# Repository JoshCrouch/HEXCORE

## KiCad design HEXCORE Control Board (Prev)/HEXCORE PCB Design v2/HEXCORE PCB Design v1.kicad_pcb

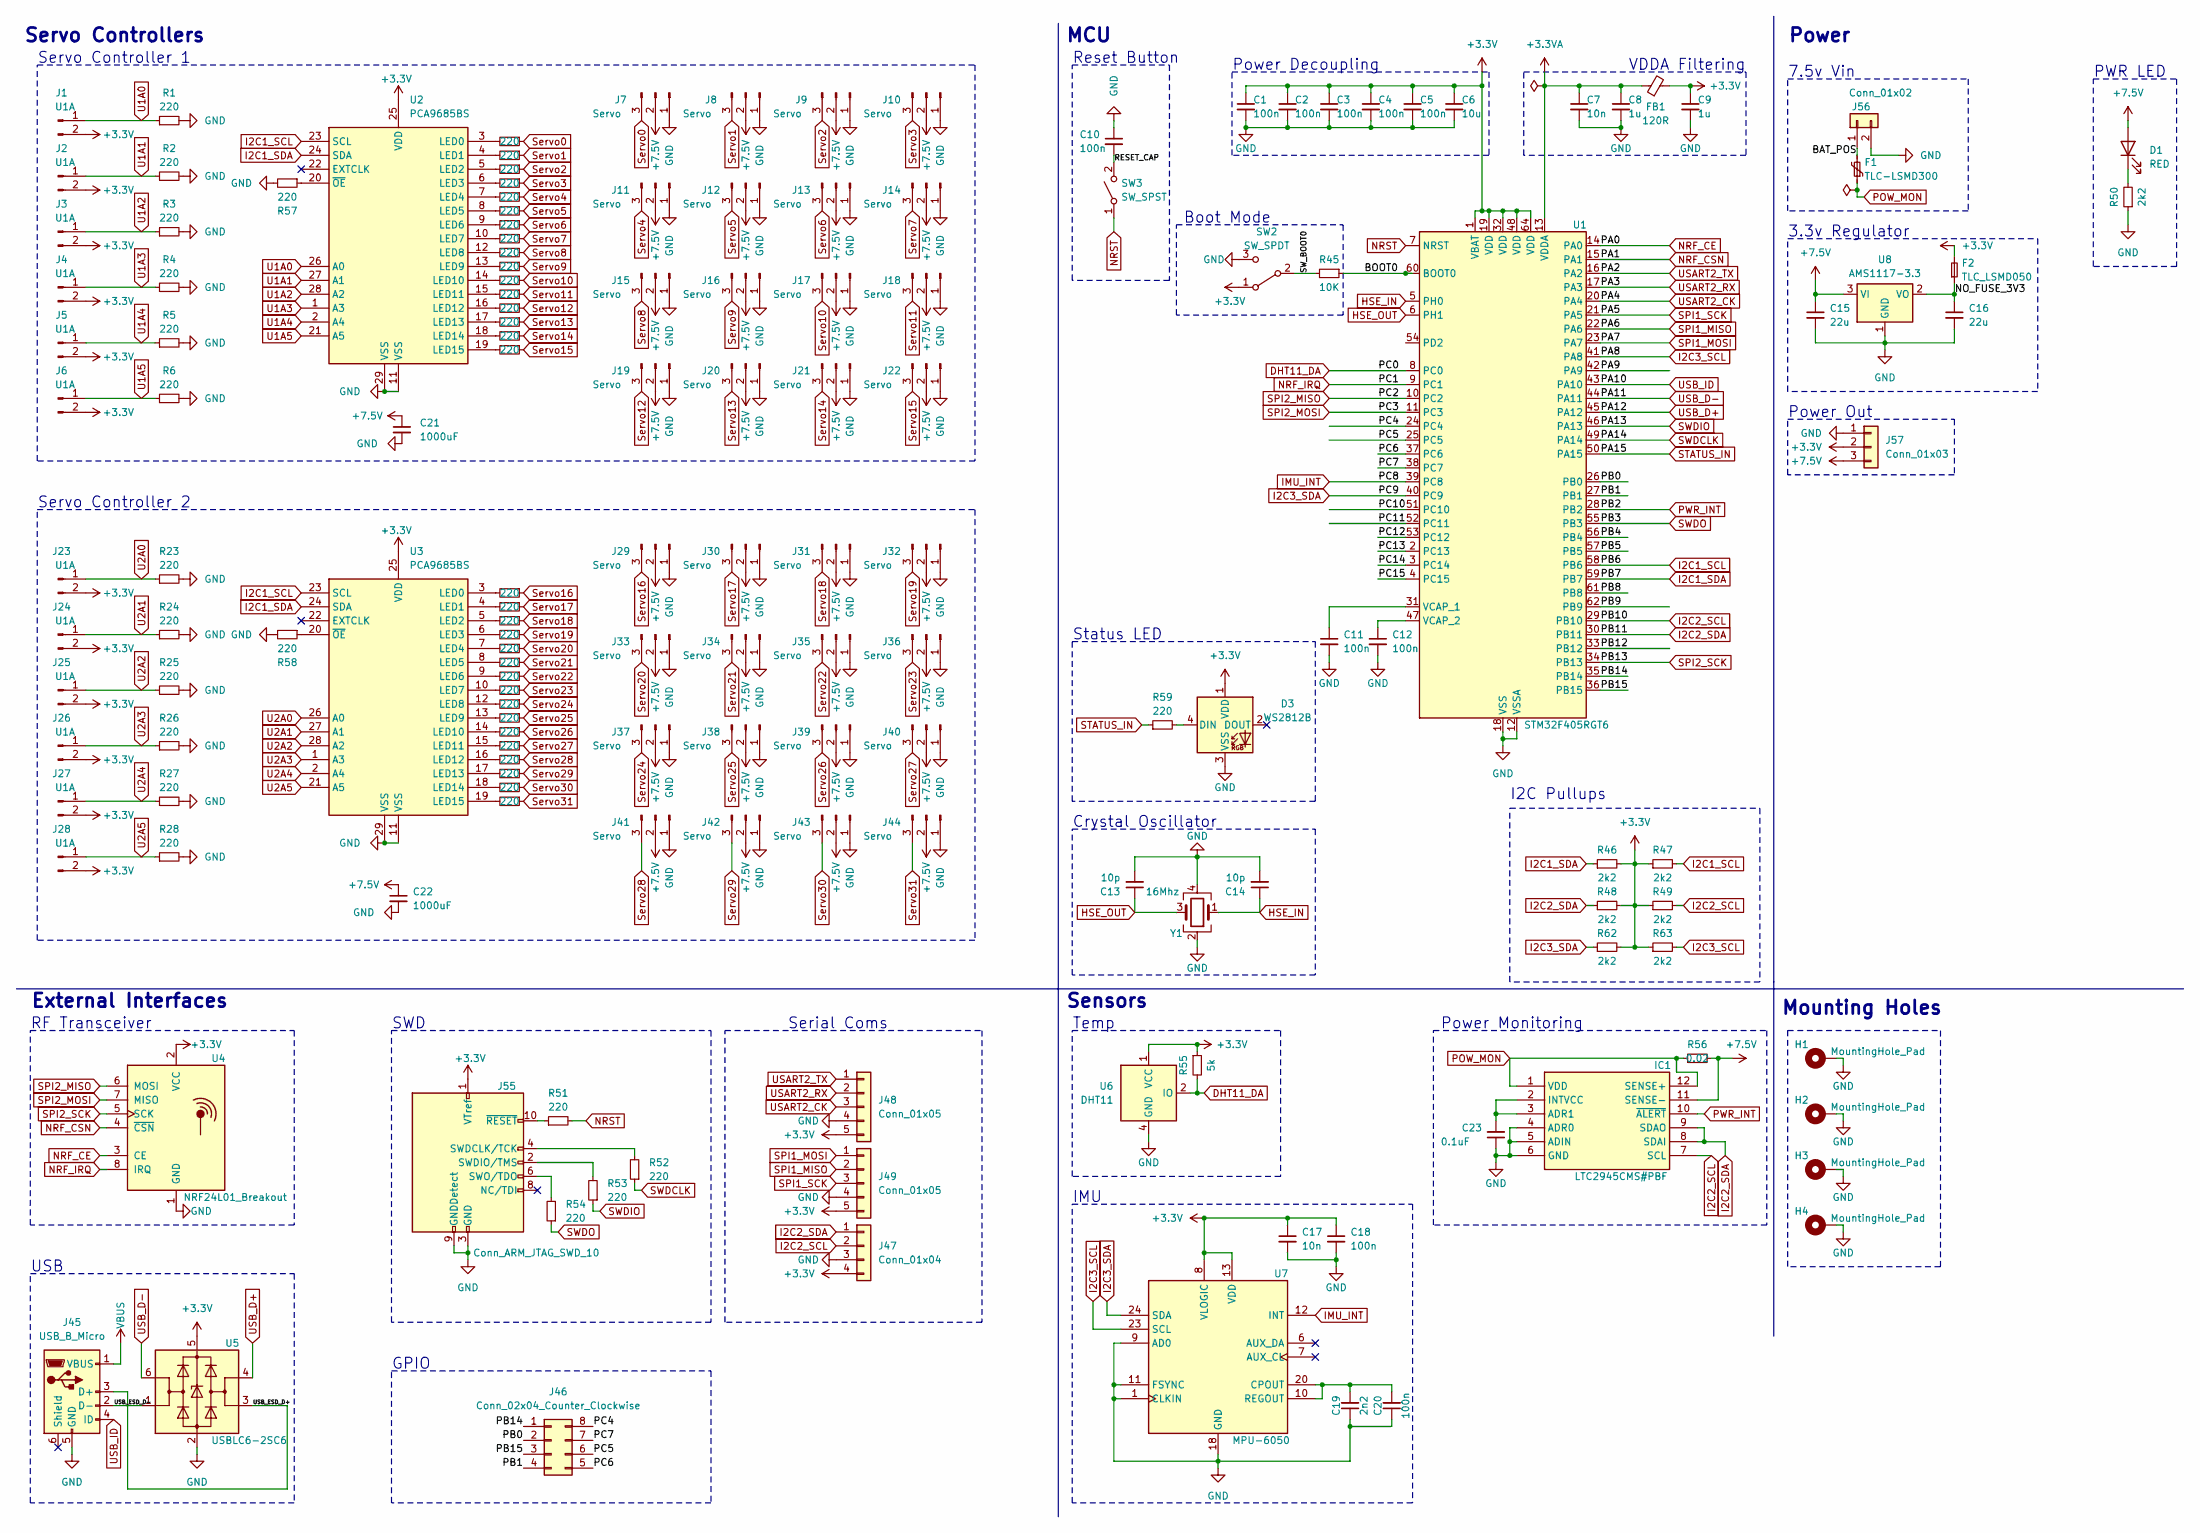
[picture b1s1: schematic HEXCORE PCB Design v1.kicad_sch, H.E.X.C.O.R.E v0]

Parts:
C1, C2, C3, C4, C5, C11, C12: 100n; C_0402_1005Metric
C6: 10u; C_0603_1608Metric
C7: 10n; C_0402_1005Metric
C8, C9: 1u; C_0402_1005Metric
C10, C18, C20: 100n; C_0201_0603Metric
C13, C14: 10p; C_0201_0603Metric
C15, C16: 22u; C_0603_1608Metric
C17: 10n; C_0201_0603Metric
C19: 2n2; C_0201_0603Metric
C21, C22: 1000uF; C_Elec_10x10.2
C23: 0.1uF; C_0201_0603Metric
D1: RED; LED_0603_1608Metric; LCSC Part C2286
D3: WS2812B; LED_WS2812B_PLCC4_5.0x5.0mm_P3.2mm; LCSC Part C2843785
F1: TLC-LSMD300; Fuse_2920_7451Metric; LCSC Part C262042
F2: TLC_LSMD050; Fuse_2920_7451Metric; LCSC Part C262037
FB1: 120R; L_0603_1608Metric
H1, H2, H3, H4: MountingHole_Pad; MountingHole_2.2mm_M2_DIN965_Pad
IC1: LTC2945CMS#PBF; SOP65P490X110-12N; Manufacturer_Part_Number LTC2945CMS#PBF; Mouser Part Number 584-LTC2945CMS#PBF
J1, J2, J3, J4, J5, J6, J23, J24, J25, J26, J27, J28: U1A; PinHeader_1x02_P2.54mm_Vertical
J7, J8, J9, J10, J11, J12, J13, J14, J15, J16, J17, J18, J19, J20, J21, J22, J29, J30, J31, J32, J33, J34, J35, J36, J37, J38, J39, J40, J41, J42, J43, J44: Servo; PinHeader_1x03_P2.54mm_Vertical
J45: USB_B_Micro; MICROXNJ; LCSC Part C404969
J46: Conn_02x04_Counter_Clockwise; PinSocket_2x04_P2.54mm_Vertical
J47: Conn_01x04; JST_XH_B4B-XH-A_1x04_P2.50mm_Vertical
J48, J49: Conn_01x05; JST_XH_B5B-XH-A_1x05_P2.50mm_Vertical
J55: Conn_ARM_JTAG_SWD_10; PinHeader_2x05_P1.27mm_Vertical
J56: Conn_01x02; AMASS_XT60-M_1x02_P7.20mm_Vertical; LCSC Part C98733
J57: Conn_01x03; JST_XH_B3B-XH-A_1x03_P2.50mm_Vertical
R1, R2, R3, R4, R5, R6, R7, R8, R9, R10, R11, R12, R13, R14, R15, R16, R17, R18, R19, R20, R21, R22, R23, R24, R25, R26, R27, R28, R29, R30, R31, R32, R33, R34, R35, R36, R37, R38, R39, R40, R41, R42, R43, R44, R51, R52, R53, R54, R57, R58, R59: 220; R_0201_0603Metric
R45: 10K; R_0201_0603Metric
R46, R47, R48, R49, R50, R62, R63: 2k2; R_0402_1005Metric
R55: 5k; R_0402_1005Metric
R56: 0.02; R_2512_6332Metric
SW2: SW_SPDT; SW_Slide_1P2T_CK_OS102011MS2Q; LCSC Part C2800116
SW3: SW_SPST; SW_SPST_B3S-1000; LCSC Part C180420
U1: STM32F405RGT6; LQFP-64_10x10mm_P0.5mm; LCSC Part C15742
U2, U3: PCA9685BS; QFN-28-1EP_6x6mm_P0.65mm_EP4.25x4.25mm; LCSC Part C5191634
U4: NRF24L01_Breakout; nRF24L01_Breakout
U5: USBLC6-2SC6; SOT-23-6; LCSC Part C2827654
U6: DHT11; Aosong_DHT11_5.5x12.0_P2.54mm; LCSC Part C117051
U7: MPU-6050; InvenSense_QFN-24_4x4mm_P0.5mm; LCSC Part C24112
U8: AMS1117-3.3; SOT-223-3_TabPin2; LCSC Part C347222
Y1: 16Mhz; Crystal_SMD_2520-4Pin_2.5x2.0mm; LCSC Part C255947

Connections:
+3.3V: C1.1, C2.1, C3.1, C4.1, C5.1, C6.1, C9.1, C17.1, C18.1, D3.1 (VDD), F2.2, FB1.2, J1.2, J2.2, J3.2, J4.2, J5.2, J6.2, J23.2, J24.2, J25.2, J26.2, J27.2, J28.2, J47.4, J48.5, J49.5, J55.1 (VTref), J57.2, R46.2, R47.1, R48.2, R49.1, R55.1, R62.2, R63.1, SW2.1 (A), U1.1 (VBAT), U1.19 (VDD), U1.32 (VDD), U1.48 (VDD), U1.64 (VDD), U2.25 (VDD), U3.25 (VDD), U4.2 (VCC), U5.5 (VBUS), U6.1 (VCC), U7.8 (VLOGIC), U7.13 (VDD)
+3.3VA: C7.1, C8.1, FB1.1, U1.13 (VDDA)
+7.5V: C15.1, C21.1, C22.1, D1.2 (A), IC1.11 (SENSE-), J7.2, J8.2, J9.2, J10.2, J11.2, J12.2, J13.2, J14.2, J15.2, J16.2, J17.2, J18.2, J19.2, J20.2, J21.2, J22.2, J29.2, J30.2, J31.2, J32.2, J33.2, J34.2, J35.2, J36.2, J37.2, J38.2, J39.2, J40.2, J41.2, J42.2, J43.2, J44.2, J57.3, R56.2, U8.3 (VI)
/BAT_POS: F1.2, J56.1
/BOOT0: R45.1, U1.60 (BOOT0)
/NO_FUSE_3V3: C16.1, F2.1, U8.2 (VO)
/PA9: U1.42 (PA9)
/PB0: J46.2, U1.26 (PB0)
/PB1: J46.4, U1.27 (PB1)
/PB4: U1.56 (PB4)
/PB5: U1.57 (PB5)
/PB8: U1.61 (PB8)
/PB9: U1.62 (PB9)
/PB12: U1.33 (PB12)
/PB14: J46.1, U1.35 (PB14)
/PB15: J46.3, U1.36 (PB15)
/PC4: J46.8, U1.24 (PC4)
/PC5: J46.6, U1.25 (PC5)
/PC6: J46.5, U1.37 (PC6)
/PC7: J46.7, U1.38 (PC7)
/PC10: U1.51 (PC10)
/PC11: U1.52 (PC11)
/PC12: U1.53 (PC12)
/PC13: U1.2 (PC13)
/PC14: U1.3 (PC14)
/PC15: U1.4 (PC15)
/RESET_CAP: C10.2, SW3.2 (B)
/SW_BOOT0: R45.2, SW2.2 (B)
/USB_ESD_D+: J45.3 (D+), U5.3 (I/O2)
/USB_ESD_D-: J45.2 (D-), U5.1 (I/O1)
DHT11_DA: R55.2, U1.8 (PC0), U6.2 (IO)
GND: C1.2, C2.2, C3.2, C4.2, C5.2, C6.2, C7.2, C8.2, C9.2, C10.1, C11.2, C12.2, C13.2, C14.2, C15.2, C16.2, C17.2, C18.2, C19.1, C20.1, C21.2, C22.2, C23.1, D3.3 (VSS), H1.1, H2.1, H3.1, H4.1, IC1.4 (ADR0), IC1.5 (ADIN), IC1.6 (GND), J7.1, J8.1, J9.1, J10.1, J11.1, J12.1, J13.1, J14.1, J15.1, J16.1, J17.1, J18.1, J19.1, J20.1, J21.1, J22.1, J29.1, J30.1, J31.1, J32.1, J33.1, J34.1, J35.1, J36.1, J37.1, J38.1, J39.1, J40.1, J41.1, J42.1, J43.1, J44.1, J45.5 (GND), J47.3, J48.4, J49.4, J55.3 (GND), J55.5 (GND), J55.9 (GNDDetect), J56.2, J57.1, R1.2, R2.2, R3.2, R4.2, R5.2, R6.2, R23.2, R24.2, R25.2, R26.2, R27.2, R28.2, R50.1, R57.2, R58.2, SW2.3 (C), U1.12 (VSSA), U1.18 (VSS), U1.63 (VSS), U2.11 (VSS), U2.29 (VSS), U3.11 (VSS), U3.29 (VSS), U4.1 (GND), U5.2 (GND), U6.4 (GND), U7.1 (CLKIN), U7.9 (AD0), U7.11 (FSYNC), U7.18 (GND), U8.1 (GND), Y1.2, Y1.4
HSE_IN: C14.1, U1.5 (PH0), Y1.1
HSE_OUT: C13.1, U1.6 (PH1), Y1.3
I2C1_SCL: R47.2, U1.58 (PB6), U2.23 (SCL), U3.23 (SCL)
I2C1_SDA: R46.1, U1.59 (PB7), U2.24 (SDA), U3.24 (SDA)
I2C2_SCL: IC1.7 (SCL), J47.2, R49.2, U1.29 (PB10)
I2C2_SDA: IC1.8 (SDAI), IC1.9 (SDAO), J47.1, R48.1, U1.30 (PB11)
I2C3_SCL: R63.2, U1.41 (PA8), U7.23 (SCL)
I2C3_SDA: R62.1, U1.40 (PC9), U7.24 (SDA)
IMU_INT: U1.39 (PC8), U7.12 (INT)
NRF_CE: U1.14 (PA0), U4.3 (CE)
NRF_CSN: U1.15 (PA1), U4.4 (~CSN)
NRF_IRQ: U1.9 (PC1), U4.8 (IRQ)
NRST: R51.2, SW3.1 (A), U1.7 (NRST)
unnamed: D1.1 (K), R50.2
unnamed: D3.4 (DIN), R59.2
unnamed: C23.2, IC1.2 (INTVCC), IC1.3 (ADR1)
unnamed: J55.4 (SWDCLK/TCK), R52.2
unnamed: J55.2 (SWDIO/TMS), R53.2
unnamed: J55.6 (SWO/TDO), R54.2
unnamed: J55.10 (~RESET), R51.1
unnamed: C11.1, U1.31 (VCAP_1)
unnamed: C12.1, U1.47 (VCAP_2)
unnamed: R7.2, U2.3 (LED0)
unnamed: R8.2, U2.4 (LED1)
unnamed: R9.2, U2.5 (LED2)
unnamed: R10.2, U2.6 (LED3)
unnamed: R11.2, U2.7 (LED4)
unnamed: R12.2, U2.8 (LED5)
unnamed: R13.2, U2.9 (LED6)
unnamed: R14.2, U2.10 (LED7)
unnamed: R15.2, U2.12 (LED8)
unnamed: R16.2, U2.13 (LED9)
unnamed: R17.2, U2.14 (LED10)
unnamed: R18.2, U2.15 (LED11)
unnamed: R19.2, U2.16 (LED12)
unnamed: R20.2, U2.17 (LED13)
unnamed: R21.2, U2.18 (LED14)
unnamed: R22.2, U2.19 (LED15)
unnamed: R57.1, U2.20 (~OE)
unnamed: R29.2, U3.3 (LED0)
unnamed: R30.2, U3.4 (LED1)
unnamed: R31.2, U3.5 (LED2)
unnamed: R32.2, U3.6 (LED3)
unnamed: R33.2, U3.7 (LED4)
unnamed: R34.2, U3.8 (LED5)
unnamed: R35.2, U3.9 (LED6)
unnamed: R36.2, U3.10 (LED7)
unnamed: R37.2, U3.12 (LED8)
unnamed: R38.2, U3.13 (LED9)
unnamed: R39.2, U3.14 (LED10)
unnamed: R40.2, U3.15 (LED11)
unnamed: R41.2, U3.16 (LED12)
unnamed: R42.2, U3.17 (LED13)
unnamed: R43.2, U3.18 (LED14)
unnamed: R44.2, U3.19 (LED15)
unnamed: R58.1, U3.20 (~OE)
unnamed: C19.2, C20.2, U7.10 (REGOUT), U7.20 (CPOUT)
POW_MON: F1.1, IC1.1 (VDD), IC1.12 (SENSE+), R56.1
PWR_INT: IC1.10 (~ALERT), U1.28 (PB2)
SPI1_MISO: J49.2, U1.22 (PA6)
SPI1_MOSI: J49.1, U1.23 (PA7)
SPI1_SCK: J49.3, U1.21 (PA5)
SPI2_MISO: U1.10 (PC2), U4.6 (MOSI)
SPI2_MOSI: U1.11 (PC3), U4.7 (MISO)
SPI2_SCK: U1.34 (PB13), U4.5 (SCK)
STATUS_IN: R59.1, U1.50 (PA15)
SWDCLK: R52.1, U1.49 (PA14)
SWDIO: R53.1, U1.46 (PA13)
SWDO: R54.1, U1.55 (PB3)
Servo0: J7.3, R7.1
Servo1: J8.3, R8.1
Servo2: J9.3, R9.1
Servo3: J10.3, R10.1
Servo4: J11.3, R11.1
Servo5: J12.3, R12.1
Servo6: J13.3, R13.1
Servo7: J14.3, R14.1
Servo8: J15.3, R15.1
Servo9: J16.3, R16.1
Servo10: J17.3, R17.1
Servo11: J18.3, R18.1
Servo12: J19.3, R19.1
Servo13: J20.3, R20.1
Servo14: J21.3, R21.1
Servo15: J22.3, R22.1
Servo16: J29.3, R29.1
Servo17: J30.3, R30.1
Servo18: J31.3, R31.1
Servo19: J32.3, R32.1
Servo20: J33.3, R33.1
Servo21: J34.3, R34.1
Servo22: J35.3, R35.1
Servo23: J36.3, R36.1
Servo24: J37.3, R37.1
Servo25: J38.3, R38.1
Servo26: J39.3, R39.1
Servo27: J40.3, R40.1
Servo28: J41.3, R41.1
Servo29: J42.3, R42.1
Servo30: J43.3, R43.1
Servo31: J44.3, R44.1
U1A0: J1.1, R1.1, U2.26 (A0)
U1A1: J2.1, R2.1, U2.27 (A1)
U1A2: J3.1, R3.1, U2.28 (A2)
U1A3: J4.1, R4.1, U2.1 (A3)
U1A4: J5.1, R5.1, U2.2 (A4)
U1A5: J6.1, R6.1, U2.21 (A5)
U2A0: J23.1, R23.1, U3.26 (A0)
U2A1: J24.1, R24.1, U3.27 (A1)
U2A2: J25.1, R25.1, U3.28 (A2)
U2A3: J26.1, R26.1, U3.1 (A3)
U2A4: J27.1, R27.1, U3.2 (A4)
U2A5: J28.1, R28.1, U3.21 (A5)
USART2_CK: J48.3, U1.20 (PA4)
USART2_RX: J48.2, U1.17 (PA3)
USART2_TX: J48.1, U1.16 (PA2)
USB_D+: U1.45 (PA12), U5.4 (I/O2)
USB_D-: U1.44 (PA11), U5.6 (I/O1)
USB_ID: J45.4 (ID), U1.43 (PA10)
VBUS: J45.1 (VBUS)

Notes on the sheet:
Power Out
Reset Button
Boot Mode
SWD
RF Transceiver
I2C Pullups
Power Monitoring
Crystal Oscillator
Sensors
USB
3.3v Regulator
Servo Controllers
PWR LED
Temp
VDDA Filtering
Servo Controller 1
GPIO
Power Decoupling
Serial Coms
External Interfaces
7.5v Vin
Mounting Holes
Power
MCU
Servo Controller 2
IMU
Status LED

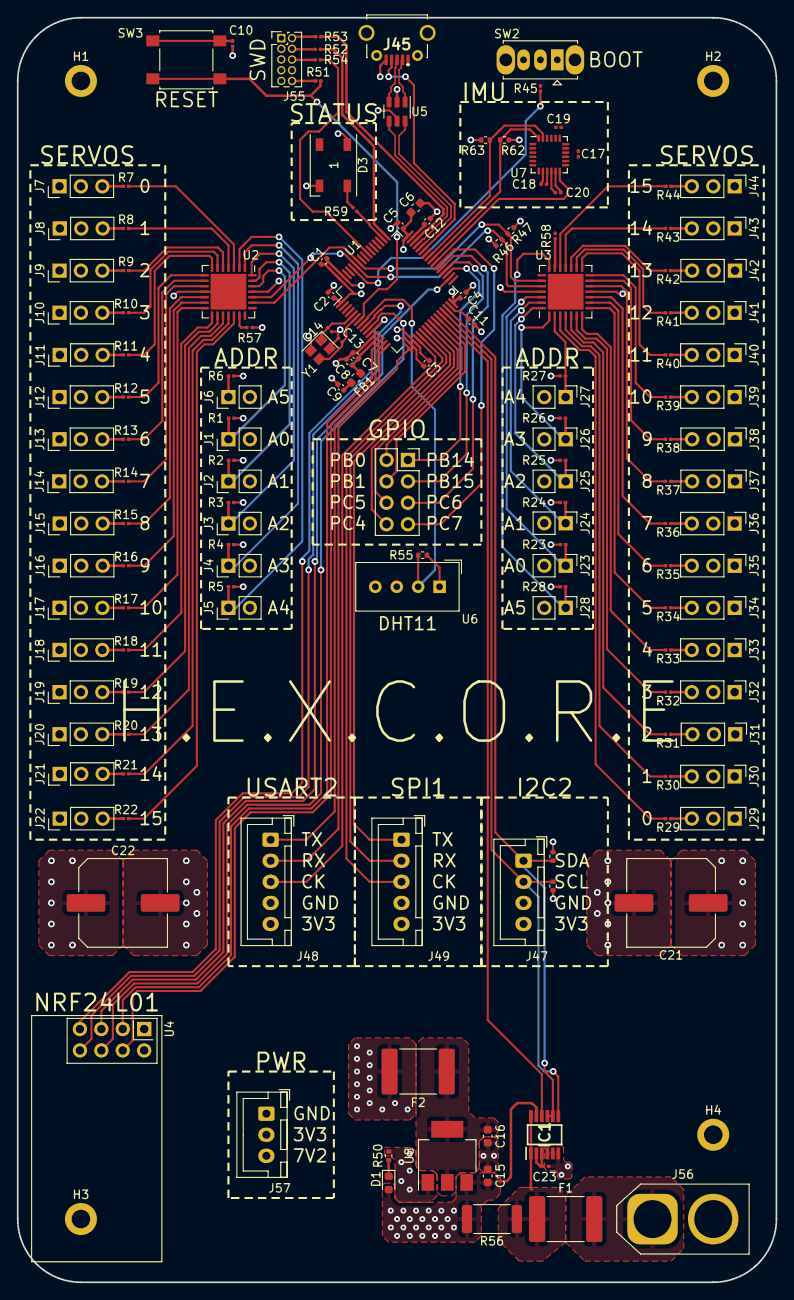
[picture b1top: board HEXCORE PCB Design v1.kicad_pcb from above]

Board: 4 copper layers, 90.0 x 150.0 mm, 157 parts (0 on the bottom side), 139 nets.

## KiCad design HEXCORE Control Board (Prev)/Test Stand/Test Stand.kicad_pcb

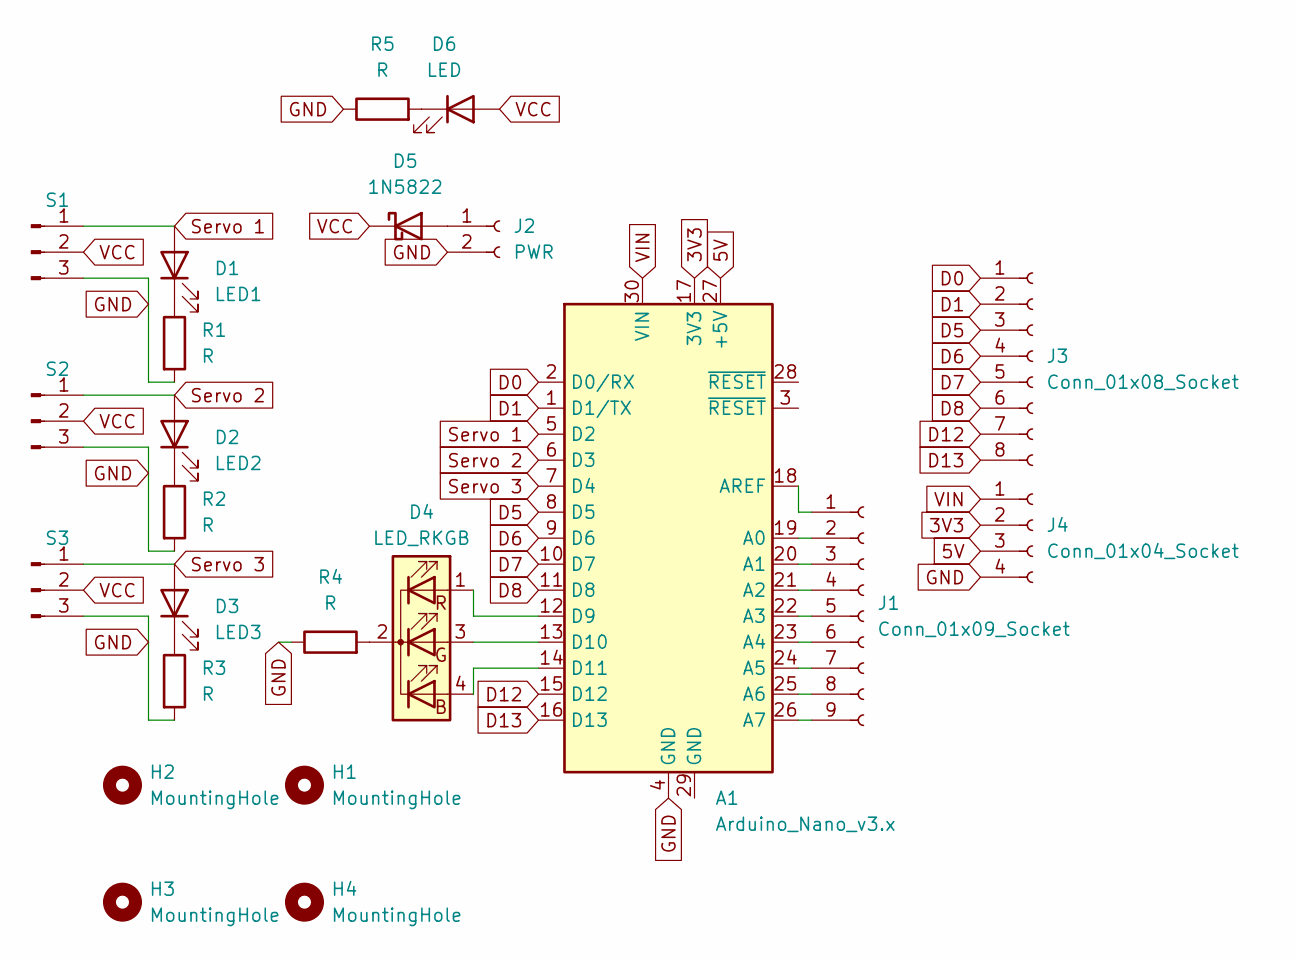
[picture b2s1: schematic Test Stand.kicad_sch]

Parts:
A1: Arduino_Nano_v3.x; Arduino_Nano
D1: LED1; LED_D5.0mm
D2: LED2; LED_D5.0mm
D3: LED3; LED_D5.0mm
D4: LED_RKGB; LED_D5.0mm-4_RGB
D5: 1N5822; D_DO-201AD_P15.24mm_Horizontal
D6: LED; LED_D5.0mm
H1, H2, H3, H4: MountingHole; MountingHole_2.2mm_M2_DIN965_Pad
J1: Conn_01x09_Socket; PinSocket_1x09_P2.54mm_Vertical
J2: PWR; PinSocket_1x02_P2.54mm_Vertical
J3: Conn_01x08_Socket; PinSocket_1x08_P2.54mm_Vertical
J4: Conn_01x04_Socket; PinSocket_1x04_P2.54mm_Vertical
R1, R2, R3, R4, R5: R; R_Axial_DIN0207_L6.3mm_D2.5mm_P10.16mm_Horizontal
S1, S2, S3: Conn_01x03_Pin; PinHeader_1x03_P2.54mm_Vertical

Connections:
3V3: A1.17 (3V3), J4.2
5V: A1.27 (+5V), J4.3
D0: A1.2 (D0/RX), J3.1
D1: A1.1 (D1/TX), J3.2
D5: A1.8 (D5), J3.3
D6: A1.9 (D6), J3.4
D7: A1.10 (D7), J3.5
D8: A1.11 (D8), J3.6
D12: A1.15 (D12), J3.7
D13: A1.16 (D13), J3.8
GND: A1.4 (GND), J2.2, J4.4, R1.2, R2.2, R3.2, R4.1, R5.1, S1.3, S2.3, S3.3
unnamed: A1.19 (A0), J1.2
unnamed: A1.20 (A1), J1.3
unnamed: A1.21 (A2), J1.4
unnamed: A1.22 (A3), J1.5
unnamed: A1.23 (A4), J1.6
unnamed: A1.24 (A5), J1.7
unnamed: A1.25 (A6), J1.8
unnamed: A1.26 (A7), J1.9
unnamed: A1.18 (AREF), J1.1
unnamed: A1.12 (D9), D4.1 (RA)
unnamed: A1.13 (D10), D4.3 (GA)
unnamed: A1.14 (D11), D4.4 (BA)
unnamed: D1.1 (K), R1.1
unnamed: D2.1 (K), R2.1
unnamed: D3.1 (K), R3.1
unnamed: D4.2 (K), R4.2
unnamed: D5.2 (A), J2.1
unnamed: D6.1 (K), R5.2
Servo 1: A1.5 (D2), D1.2 (A), S1.1
Servo 2: A1.6 (D3), D2.2 (A), S2.1
Servo 3: A1.7 (D4), D3.2 (A), S3.1
VCC: D5.1 (K), D6.2 (A), S1.2, S2.2, S3.2
VIN: A1.30 (VIN), J4.1

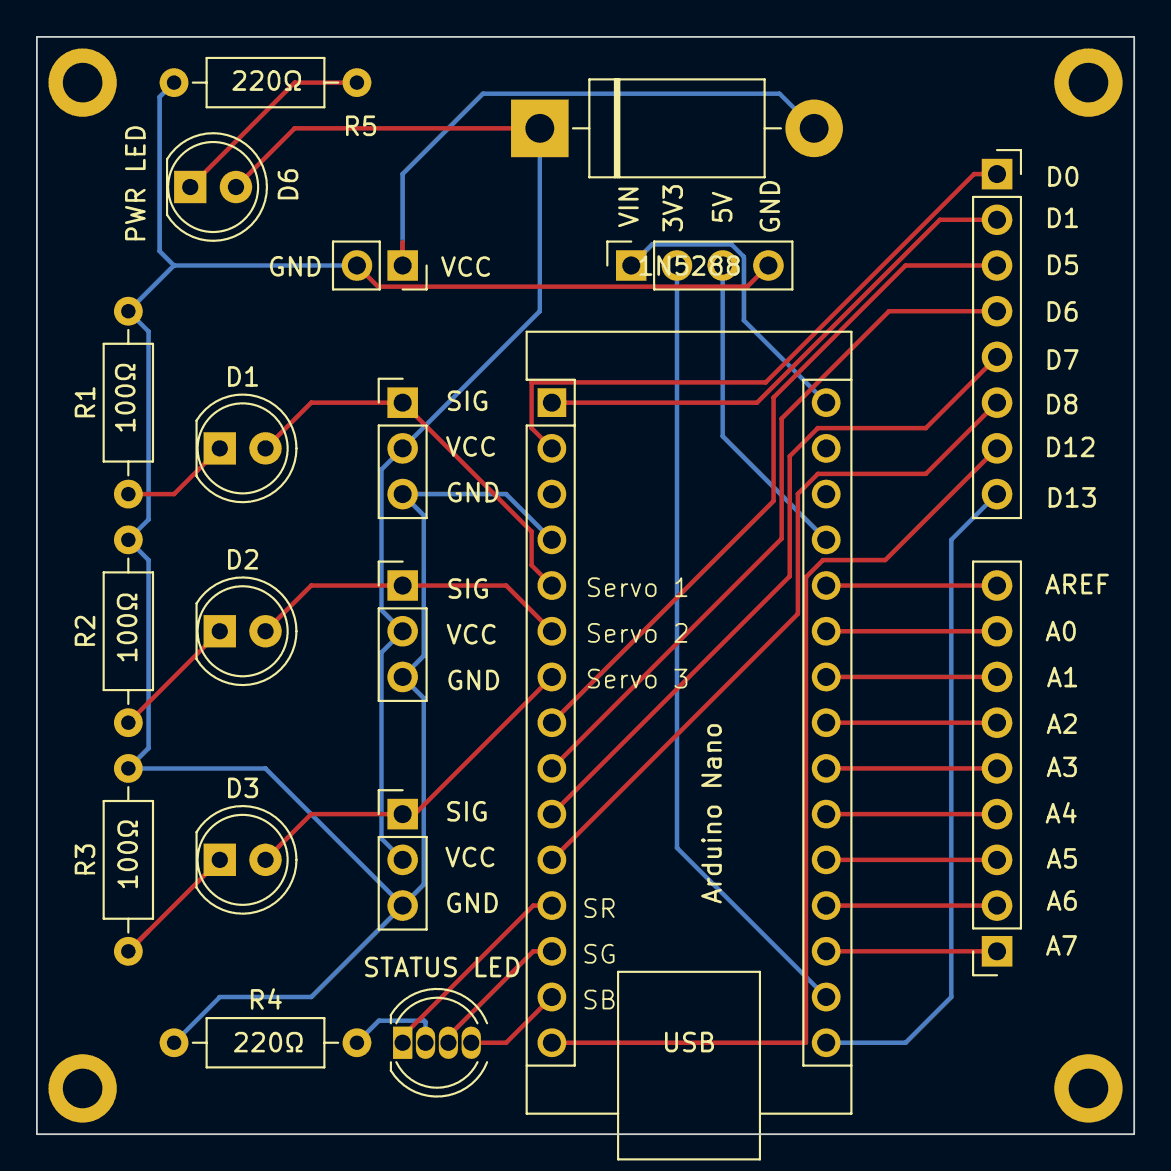
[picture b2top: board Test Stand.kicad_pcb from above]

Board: 2 copper layers, 61.0 x 61.0 mm, 23 parts (0 on the bottom side), 34 nets.

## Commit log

2024-03-03 Initial Commit
    Moving all files to GitHub
2024-03-03 Added Control Board
    Had to delete the .git file added by Altium to be able to commit this part.
2024-08-26 Added development code working on the inverse kinematics for a single leg.
